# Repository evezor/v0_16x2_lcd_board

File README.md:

# 16x2 LCD Board
*please note this board is has been deprecated.

This board uses the Evezor Stamp STMF405 MCU

source: https://github.com/evezor/Evezor-Stamp-STMF405

An edge board with a 16 x 2 LCD module.

Evezor® and all associated marks, logos, and designs are registered trademarks and protected by copyright. Unauthorized use or reproduction of these trademarks and copyrighted materials is strictly prohibited.

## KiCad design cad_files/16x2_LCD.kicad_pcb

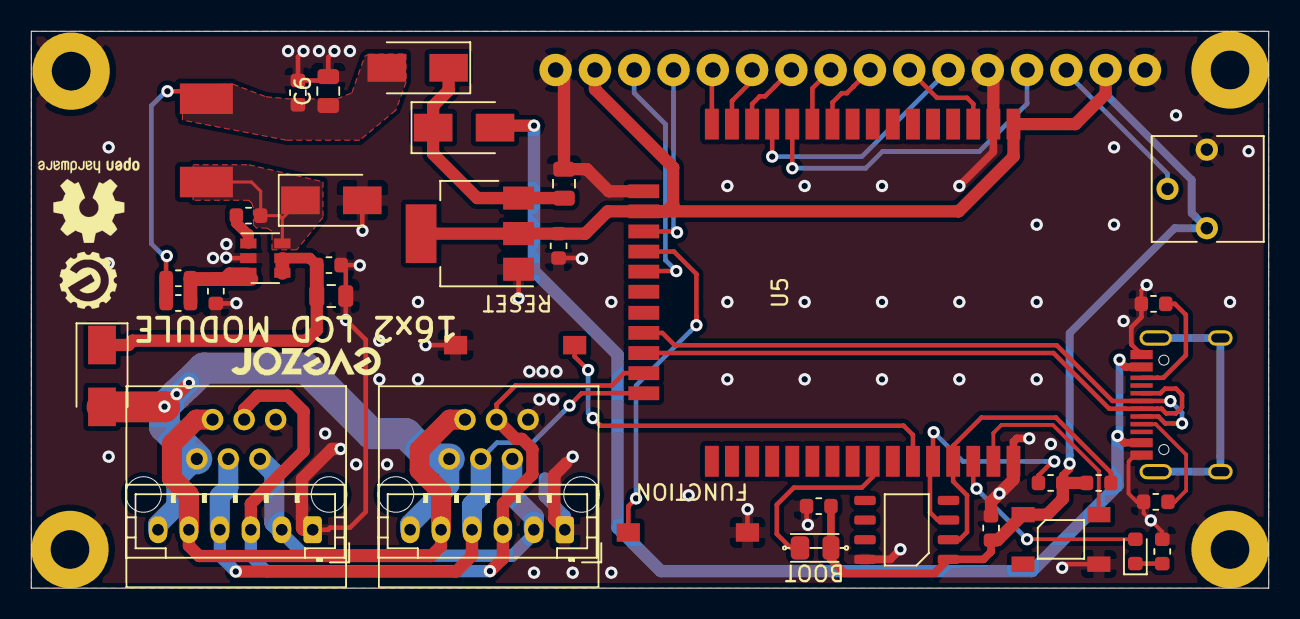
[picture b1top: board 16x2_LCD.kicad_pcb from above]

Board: 2 copper layers, 80.0 x 36.0 mm, 42 parts (1 on the bottom side), 37 nets.

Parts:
C1, C2, C3, C5, C7, C10: .1uF; C_0603_1608Metric
C4: 4.7uF; C_0805_2012Metric
C6: 22uF; C_0805_2012Metric
C8: 10uF; C_0805_2012Metric
C9: C_Small; C_0603_1608Metric
D1, D2, D4, D5: D_Schottky; D_SMA
D3: LED; LED_0603_1608Metric
H1, H2, H3, H4: MountingHole_Pad; MountingHole_2.5mm_Pad
J1: USB_C_Receptacle_USB2.0; USB_C_Receptacle_HRO_TYPE-C-31-M-12
J2, J3: RJ11; RJ11_C189747_Horizontal
J4, J5: PH; JST_PH_B6B-PH-K_1x06_P2.00mm_Vertical
JP1: Jumper_NO_Small; SHORT_PAD
L1: 22uH; INDUCTOR_7.5X6.6_GCDA0630-220MC
R1, R5: 15k; R_0603_1608Metric
R2: 82k; R_0603_1608Metric
R3, R4: 5.1k; R_0603_1608Metric
R6, R7: 4.7k; R_0603_1608Metric
RV1: R_POT; Potentiometer_Vishay_T73YP_Vertical
SW1, SW2: SW_Push; SWITCH_2x3_SMD_TACTILE_GREEN
U1: V_REG; SOT-23-6
U2: AMS1117-3.3; SOT-223-3_TabPin2
U3: MICOCONTROLLER_GUID_SOP-8; GUID_PS150C
U4: RC1602A; 16X2_LCD_3.3V
U5: EDGE_STM32F405_CPU_V1; EDGE_STAMP
U6: NEOPIXEL_5050

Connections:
+3V3: C7.1, C9.1, C10.1, JP1.2, R6.1, R7.1, RV1.3, U2.2, U3.1, U4.2, U4.15, U5.1, U5.18, U6.1
+48V: D2.2, J2.6, J3.6, J4.6, J5.6
/BOOT: JP1.1, U5.36
/CAN_H: J2.3, J3.3, J4.3, J5.3, U5.26
/CAN_L: J2.4, J3.4, J4.4, J5.4, U5.27
/D+: J1.A6, J1.B6, U5.25
/D-: J1.A7, J1.B7, U5.24
/DB0: U4.7, U5.3
/DB1: U4.8, U5.10
/DB2: U4.9, U5.11
/DB3: U4.10, U5.14
/DB4: U4.11, U5.15
/DB5: U4.12, U5.16
/DB6: U4.13, U5.19
/DB7: U4.14, U5.21
/E: U4.6, U5.13
/FD_H: J2.2, J3.2, J4.2, J5.2
/FD_L: J2.5, J3.5, J4.5, J5.5
/FUNCTION: SW2.1, U5.20
/GUID_SDA: R7.2, U3.3, U5.39
/GUID_SDO: R6.2, U3.2, U5.40
/NEO_STATUS: U5.42, U6.4
/RESET: SW1.1, U5.38
/RS: U4.4, U5.12
/USB_VCC: D4.2, J1.A4, J1.A9, J1.B4, J1.B9
/VREG: C2.1, C5.1, C6.1, D5.2, L1.2, R2.1
GND: C3.2, C4.2, C5.2, C6.2, C7.2, C8.2, C9.2, C10.2, D1.2, H1.1, H2.1, H3.1, H4.1, J1.A1, J1.A12, J1.B1, J1.B12, J2.1, J3.1, J4.1, J5.1, R1.1, R3.2, R4.2, R5.1, RV1.1, SW1.2, SW2.2, U1.2, U2.1, U3.8, U4.1, U4.5, U4.16, U5.2, U5.17, U5.43, U6.3
unnamed: C1.1, D1.1, L1.1, U1.6
unnamed: C1.2, U1.1
unnamed: C2.2, R1.2, R2.2, U1.3
unnamed: C3.1, C4.1, D2.1, U1.4, U1.5
unnamed: C8.1, D4.1, D5.1, U2.3
unnamed: D3.1, R5.2
unnamed: D3.2, U5.41
unnamed: J1.A5, R4.1
unnamed: J1.B5, R3.1
unnamed: RV1.2, U4.3

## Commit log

2020-11-06 inital commit
2020-11-20 add example code
2021-04-28 update baudrate
2021-04-28 time
2021-05-09 shows channels and more
2023-09-11 add pics
2023-09-11 Create LICENSE
